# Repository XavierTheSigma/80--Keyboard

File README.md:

# Keyboard
My Keyboard is a standard 80% keyboard with an added Rotary Encoder for volume control.

I made this Keyboard for myself, And to learn. This was my first time using Chip on Board tech, so it was quite a challenge for me, but it helped me learn alot.

## Features:
- 80% Keyboard
- 87 Keys
- Rotary Encoder 
- Arrow Keys
- F Keys
- Chip On Board

## CAD Model:
I designed the Case to fit together with 3 pieces and 8 M2.5 screws. The 3 pieces are the Bottom of the case, The sides of the case (with a cutout for the USB-C) and the Top of the case, which includes the switch plate and the Top Frame. The Bottom and Sides are clearance holes and the screw threads into the top. The screw threads into 1.4mm of the top part and the screws are actually held .5mm higher than the bottom instead of flush.

## PCB:
I made my PCB in KiCad. This was my first time using CoB, Chip on Board, where instead of using a microcontroller, The RP2040 chip is directly on the board with all the other necessary components. I ended up reffereing to [RP2040 Datasheet](https://pip.raspberrypi.com/documents/RP-008371-DS-rp2040-datasheet.pdf) alot for this. 

Here is the Schematic, I spend alot of time figuring out how to get the whole CoB system working, but I think I did well.

Here is the PCB, I think I was able to make it pretty Compact with the components, however I am still unsure about the USB-C port.

## Firmware:
I decided on [KMK](https://github.com/KMKfw/kmk_firmware) firmware for this keyboard, as it is quite easy to code and implement.

## BOM:
|Name                    |Purpose                     |Quantity|Total Cost (USD)|Link                                                                                                                                                                                                                                                                                                                                                                                                                                                                                                                                                                                                                                                                           |Distributor|
|------------------------|----------------------------|--------|----------------|-------------------------------------------------------------------------------------------------------------------------------------------------------------------------------------------------------------------------------------------------------------------------------------------------------------------------------------------------------------------------------------------------------------------------------------------------------------------------------------------------------------------------------------------------------------------------------------------------------------------------------------------------------------------------------|-----------|
|M2.5x12mm Screws        |Hold the Case Together      |100     |4.29            |https://www.aliexpress.com/item/1005006149650871.html?spm=a2g0o.productlist.main.7.351a5435pfKSzT&algo_pvid=73726b03-3458-4531-a617-164769dc475a&algo_exp_id=73726b03-3458-4531-a617-164769dc475a-6&pdp_ext_f=%7B%22order%22%3A%22815%22%2C%22spu_best_type%22%3A%22price%22%2C%22eval%22%3A%221%22%2C%22fromPage%22%3A%22search%22%7D&pdp_npi=6%40dis%21AUD%214.29%214.29%21%21%2120.05%2120.05%21%4021033d9d17748774623062062ebf6b%2112000035985037198%21sea%21AU%216079532204%21X%211%210%21n_tag%3A-29919%3Bd%3A8c80d33f%3Bm03_new_user%3A-29895&curPageLogUid=wg6dSTH9tu8G&utparam-url=scene%3Asearch%7Cquery_from%3A%7Cx_object_id%3A1005006149650871%7C_p_origin_prod%3A|Aliexpress |
|PCBA                    |Printed Circuit Board       |2       |53.90           |https://cart.jlcpcb.com/shopcart/cart                                                                                                                                                                                                                                                                                                                                                                                                                                                                                                                                                                                                                                          |JLCPCB     |
|3x4mm SMD tactile switch|BOOT and RESET              |100     |3.04            |https://www.aliexpress.com/item/1005005551946922.html?spm=a2g0o.cart.0.0.6cea38daTwsp4M&mp=1&pdp_npi=6%40dis%21AUD%21AUD%204.43%21AUD%204.43%21%21AUD%204.34%21%21%21%402103274e17748741857928605e241d%2112000033511703865%21ct%21AU%216079532204%21%211%210%21                                                                                                                                                                                                                                                                                                                                                                                                                |Aliexpress |
|Hotswap Sockets         |For the switches to go into.|110     |6.78            |https://www.aliexpress.com/item/1005007232040760.html?spm=a2g0o.cart.0.0.691238daXmoF8z&mp=1&pdp_npi=6%40dis%21AUD%21AUD%2021.04%21AUD%209.89%21%21AUD%209.79%21%21%21%402101d6ff17748726457652554ef3f5%2112000039893759777%21ct%21AU%216079532204%21%211%210%21                                                                                                                                                                                                                                                                                                                                                                                                               |Aliexpress |
|Rotary Encoder          |Volume Control              |2       |2.33            |https://www.aliexpress.com/item/1005009360298765.html?spm=a2g0o.cart.0.0.691238daXmoF8z&mp=1&pdp_npi=6%40dis%21AUD%21AUD%207.09%21AUD%203.40%21%21AUD%203.37%21%21%21%402101d6ff17748726457652554ef3f5%2112000049239221996%21ct%21AU%216079532204%21%211%210%21                                                                                                                                                                                                                                                                                                                                                                                                                |Aliexpress |
|Mechanical Switches     |Register Keystrokes         |90      |11.10           |https://www.aliexpress.com/item/1005010733013518.html?spm=a2g0o.cart.0.0.691238daXmoF8z&mp=1&pdp_npi=6%40dis%21AUD%21AUD%205.39%21AUD%205.39%21%21AUD%205.39%21%21%21%402101d6ff17748726457652554ef3f5%2112000053347971169%21ct%21AU%216079532204%21%213%210%21                                                                                                                                                                                                                                                                                                                                                                                                                |Aliexpress |
|Keycap Set              |To press on                 |1       |12.61           |https://www.aliexpress.com/item/1005009316481772.html?spm=a2g0o.cart.0.0.691238daXmoF8z&mp=1&pdp_npi=6%40dis%21AUD%21AUD%2018.39%21AUD%2018.39%21%21AUD%2018.39%21%21%21%402101d6ff17748723426904626ef3f5%2112000048726412320%21ct%21AU%216079532204%21%211%210%21                                                                                                                                                                                                                                                                                                                                                                                                             |Aliexpress |
|Stabilizers             |Prevent Wobbling            |1       |2.60            |https://www.aliexpress.com/item/1005007212869086.html?spm=a2g0o.cart.0.0.691238daXmoF8z&mp=1&pdp_npi=6%40dis%21AUD%21AUD%203.79%21AUD%203.79%21%21AUD%203.79%21%21%21%402101d6ff17748723426904626ef3f5%2112000039826435204%21ct%21AU%216079532204%21%211%210%21                                                                                                                                                                                                                                                                                                                                                                                                                |Aliexpress |
|1N5819 Diode (SMD)      |Diodes for Matrix           |100     |2.03            |https://www.aliexpress.com/item/1005010391501956.html?mp=1&pdp_npi=6%40dis%21AUD%21AUD%202.96%21AUD%202.96%21%21AUD%202.87%21%21%21%402101d6ff17748723426904626ef3f5%2112000052256220506%21ct%21AU%216079532204%21%211%210%21                                                                                                                                                                                                                                                                                                                                                                                                                                                  |Aliexpress |
|                        |                            |        |                |                                                                                                                                                                                                                                                                                                                                                                                                                                                                                                                                                                                                                                                                               |           |

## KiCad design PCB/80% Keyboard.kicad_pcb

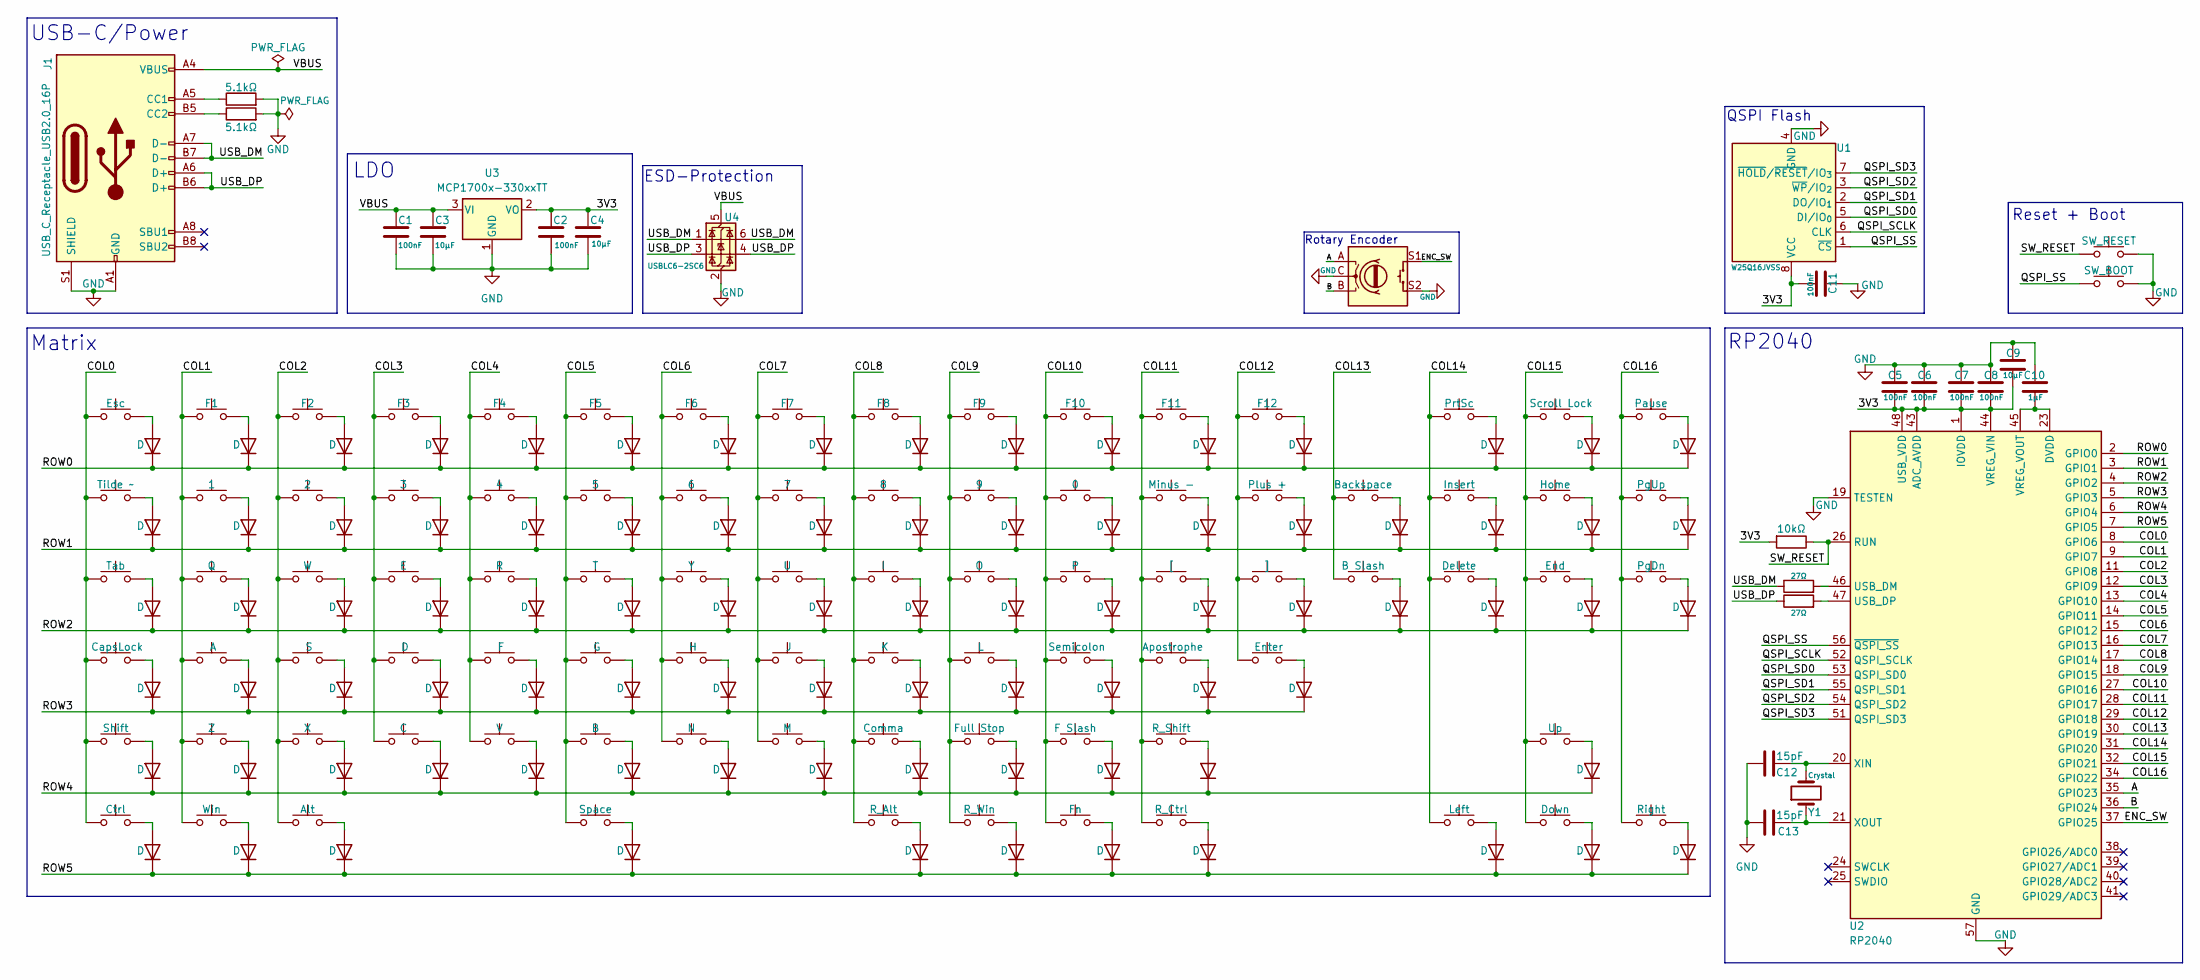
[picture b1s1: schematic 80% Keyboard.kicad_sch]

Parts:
C1, C2, C5, C6, C7, C8, C11: 100nF; C_0402_1005Metric_Pad0.74x0.62mm_HandSolder
C3, C4, C9: 10µF; C_0402_1005Metric_Pad0.74x0.62mm_HandSolder
C10: 1µF; C_0402_1005Metric_Pad0.74x0.62mm_HandSolder
C12, C13: 15pF; C_0402_1005Metric_Pad0.74x0.62mm_HandSolder
D1, D2, D3, D4, D5, D6, D7, D8, D9, D10, D11, D12, D13, D14, D15, D16, D17, D18, D19, D20, D21, D22, D23, D25, D26, D27, D28, D29, D31, D32, D33, D34, D35, D36, D37, D38, D39, D40, D41, D43, D44, D45, D46, D47, D49, D50, D51, D52, D53, D54, D55, D56, D57, D58, D59, D60, D61, D62, D63, D64, D65, D66, D67, D68, D69, D70, D71, D72, D73, D74, D75, D76, D80, D81, D85, D86, D87, D90, D91, D92, D93, D95, D96, D97, D98, D99, D102: D; D_SOD-123
J1: USB_C_Receptacle_USB2.0_16P; USB_C_Receptacle_GCT_USB4105-xx-A_16P_TopMnt_Horizontal
R1, R2: 5.1kΩ; R_0402_1005Metric_Pad0.72x0.64mm_HandSolder
R3: 10kΩ; R_0402_1005Metric_Pad0.72x0.64mm_HandSolder
R4, R5: 27Ω; R_0402_1005Metric_Pad0.72x0.64mm_HandSolder
SW1: Esc; MX-Hotswap-1U
SW2: Tilde ~; MX-Hotswap-1U
SW3: Tab; MX-Hotswap-1.5U
SW4: CapsLock; MX-Hotswap-1.75U
SW5: Shift; MX-Hotswap-2.25U
SW6: Ctrl; MX-Hotswap-1.25U
SW7: F1; MX-Hotswap-1U
SW8: 1; MX-Hotswap-1U
SW9: Q; MX-Hotswap-1U
SW10: A; MX-Hotswap-1U
SW11: Z; MX-Hotswap-1U
SW12: Win; MX-Hotswap-1.25U
SW13: F2; MX-Hotswap-1U
SW14: 2; MX-Hotswap-1U
SW15: W; MX-Hotswap-1U
SW16: S; MX-Hotswap-1U
SW17: X; MX-Hotswap-1U
SW18: Alt; MX-Hotswap-1.25U
SW19: F3; MX-Hotswap-1U
SW20: 3; MX-Hotswap-1U
SW21: E; MX-Hotswap-1U
SW22: D; MX-Hotswap-1U
SW23: C; MX-Hotswap-1U
SW24: RotaryEncoder; RotaryEncoder_Alps_EC11E-Switch_Vertical_H20mm
SW25: F4; MX-Hotswap-1U
SW26: 4; MX-Hotswap-1U
SW27: R; MX-Hotswap-1U
SW28: F; MX-Hotswap-1U
SW29: V; MX-Hotswap-1U
SW30: SW_BOOT; SW_Push_1P1T_NO_Vertical_Wuerth_434133025816
SW31: F5; MX-Hotswap-1U
SW32: 5; MX-Hotswap-1U
SW33: T; MX-Hotswap-1U
SW34: G; MX-Hotswap-1U
SW35: B; MX-Hotswap-1U
SW36: Space; MX-Hotswap-6.25U
SW37: F6; MX-Hotswap-1U
SW38: 6; MX-Hotswap-1U
SW39: Y; MX-Hotswap-1U
SW40: H; MX-Hotswap-1U
SW41: N; MX-Hotswap-1U
SW42: SW_RESET; SW_Push_1P1T_NO_Vertical_Wuerth_434133025816
SW43: F7; MX-Hotswap-1U
SW44: 7; MX-Hotswap-1U
SW45: U; MX-Hotswap-1U
SW46: J; MX-Hotswap-1U
SW47: M; MX-Hotswap-1U
SW49: F8; MX-Hotswap-1U
SW50: 8; MX-Hotswap-1U
SW51: I; MX-Hotswap-1U
SW52: K; MX-Hotswap-1U
SW53: Comma; MX-Hotswap-1U
SW54: R_Alt; MX-Hotswap-1.25U
SW55: F9; MX-Hotswap-1U
SW56: 9; MX-Hotswap-1U
SW57: O; MX-Hotswap-1U
SW58: L; MX-Hotswap-1U
SW59: Full Stop; MX-Hotswap-1U
SW60: R_Win; MX-Hotswap-1.25U
SW61: F10; MX-Hotswap-1U
SW62: 0; MX-Hotswap-1U
SW63: P; MX-Hotswap-1U
SW64: Semicolon; MX-Hotswap-1U
SW65: F Slash; MX-Hotswap-1U
SW66: Fn; MX-Hotswap-1.25U
SW67: F11; MX-Hotswap-1U
SW68: Minus -; MX-Hotswap-1U
SW69: [; MX-Hotswap-1U
SW70: Apostrophe; MX-Hotswap-1U
SW71: R_Shift; MX-Hotswap-2.75U
SW72: R_Ctrl; MX-Hotswap-1.25U
SW73: F12; MX-Hotswap-1U
SW74: Plus +; MX-Hotswap-1U
SW75: ]; MX-Hotswap-1U
SW76: Enter; MX-Hotswap-2.25U
SW80: Backspace; MX-Hotswap-2U
SW81: B Slash; MX-Hotswap-1.5U
SW85: PrtSc; MX-Hotswap-1U
SW86: Insert; MX-Hotswap-1U
SW87: Delete; MX-Hotswap-1U
SW90: Left; MX-Hotswap-1U
SW91: Scroll Lock; MX-Hotswap-1U
SW92: Home; MX-Hotswap-1U
SW93: End; MX-Hotswap-1U
SW95: Up; MX-Hotswap-1U
SW96: Down; MX-Hotswap-1U
SW97: Pause; MX-Hotswap-1U
SW98: PgUp; MX-Hotswap-1U
SW99: PgDn; MX-Hotswap-1U
SW102: Right; MX-Hotswap-1U
U1: W25Q16JVSS; SOIC-8_3.9x4.9mm_P1.27mm
U2: RP2040; QFN-56-1EP_7x7mm_P0.4mm_EP3.2x3.2mm
U3: MCP1700x-330xxTT; SOT-23
U4: USBLC6-2SC6; SOT-23-6
Y1: Crystal; Crystal_SMD_3225-4Pin_3.2x2.5mm_HandSoldering

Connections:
/3V3: C2.1, C4.1, C5.2, C6.2, C7.2, C8.2, C9.2, C11.2, R3.2, U1.8 (VCC), U2.1 (IOVDD), U2.10 (IOVDD), U2.22 (IOVDD), U2.33 (IOVDD), U2.42 (IOVDD), U2.43 (ADC_AVDD), U2.44 (VREG_VIN), U2.48 (USB_VDD), U2.49 (IOVDD), U3.2 (VO)
/A: SW24.A, U2.35 (GPIO23)
/B: SW24.B, U2.36 (GPIO24)
/COL0: SW1.1, SW2.1, SW3.1, SW4.1, SW5.1, SW6.1, U2.8 (GPIO6)
/COL1: SW7.1, SW8.1, SW9.1, SW10.1, SW11.1, SW12.1, U2.9 (GPIO7)
/COL2: SW13.1, SW14.1, SW15.1, SW16.1, SW17.1, SW18.1, U2.11 (GPIO8)
/COL3: SW19.1, SW20.1, SW21.1, SW22.1, SW23.1, U2.12 (GPIO9)
/COL4: SW25.1, SW26.1, SW27.1, SW28.1, SW29.1, U2.13 (GPIO10)
/COL5: SW31.1, SW32.1, SW33.1, SW34.1, SW35.1, SW36.1, U2.14 (GPIO11)
/COL6: SW37.1, SW38.1, SW39.1, SW40.1, SW41.1, U2.15 (GPIO12)
/COL7: SW43.1, SW44.1, SW45.1, SW46.1, SW47.1, U2.16 (GPIO13)
/COL8: SW49.1, SW50.1, SW51.1, SW52.1, SW53.1, SW54.1, U2.17 (GPIO14)
/COL9: SW55.1, SW56.1, SW57.1, SW58.1, SW59.1, SW60.1, U2.18 (GPIO15)
/COL10: SW61.1, SW62.1, SW63.1, SW64.1, SW65.1, SW66.1, U2.27 (GPIO16)
/COL11: SW67.1, SW68.1, SW69.1, SW70.1, SW71.1, SW72.1, U2.28 (GPIO17)
/COL12: SW73.1, SW74.1, SW75.1, SW76.1, U2.29 (GPIO18)
/COL13: SW80.1, SW81.1, U2.30 (GPIO19)
/COL14: SW85.1, SW86.1, SW87.1, SW90.1, U2.31 (GPIO20)
/COL15: SW91.1, SW92.1, SW93.1, SW95.1, SW96.1, U2.32 (GPIO21)
/COL16: SW97.1, SW98.1, SW99.1, SW102.1, U2.34 (GPIO22)
/ENC_SW: SW24.S1, U2.37 (GPIO25)
/QSPI_SCLK: U1.6 (CLK), U2.52 (QSPI_SCLK)
/QSPI_SD0: U1.5 (DI/IO_{0}), U2.53 (QSPI_SD0)
/QSPI_SD1: U1.2 (DO/IO_{1}), U2.55 (QSPI_SD1)
/QSPI_SD2: U1.3 (~WP/IO_{2}), U2.54 (QSPI_SD2)
/QSPI_SD3: U1.7 (~HOLD/~RESET/IO_{3}), U2.51 (QSPI_SD3)
/QSPI_SS: SW30.1, U1.1 (~CS), U2.56 (~QSPI_SS)
/ROW0: D1.1 (K), D7.1 (K), D13.1 (K), D19.1 (K), D25.1 (K), D31.1 (K), D37.1 (K), D43.1 (K), D49.1 (K), D55.1 (K), D61.1 (K), D67.1 (K), D73.1 (K), D85.1 (K), D91.1 (K), D97.1 (K), U2.2 (GPIO0)
/ROW1: D2.1 (K), D8.1 (K), D14.1 (K), D20.1 (K), D26.1 (K), D32.1 (K), D38.1 (K), D44.1 (K), D50.1 (K), D56.1 (K), D62.1 (K), D68.1 (K), D74.1 (K), D80.1 (K), D86.1 (K), D92.1 (K), D98.1 (K), U2.3 (GPIO1)
/ROW2: D3.1 (K), D9.1 (K), D15.1 (K), D21.1 (K), D27.1 (K), D33.1 (K), D39.1 (K), D45.1 (K), D51.1 (K), D57.1 (K), D63.1 (K), D69.1 (K), D75.1 (K), D81.1 (K), D87.1 (K), D93.1 (K), D99.1 (K), U2.4 (GPIO2)
/ROW3: D4.1 (K), D10.1 (K), D16.1 (K), D22.1 (K), D28.1 (K), D34.1 (K), D40.1 (K), D46.1 (K), D52.1 (K), D58.1 (K), D64.1 (K), D70.1 (K), D76.1 (K), U2.5 (GPIO3)
/ROW4: D5.1 (K), D11.1 (K), D17.1 (K), D23.1 (K), D29.1 (K), D35.1 (K), D41.1 (K), D47.1 (K), D53.1 (K), D59.1 (K), D65.1 (K), D71.1 (K), D95.1 (K), U2.6 (GPIO4)
/ROW5: D6.1 (K), D12.1 (K), D18.1 (K), D36.1 (K), D54.1 (K), D60.1 (K), D66.1 (K), D72.1 (K), D90.1 (K), D96.1 (K), D102.1 (K), U2.7 (GPIO5)
/SW_RESET: R3.1, SW42.1, U2.26 (RUN)
/USB_DM: J1.A7 (D-), J1.B7 (D-), R4.1, U4.1 (I/O1), U4.6 (I/O1)
/USB_DP: J1.A6 (D+), J1.B6 (D+), R5.1, U4.3 (I/O2), U4.4 (I/O2)
/VBUS: C1.1, C3.1, J1.A4 (VBUS), J1.A9 (VBUS), J1.B4 (VBUS), J1.B9 (VBUS), U3.3 (VI), U4.5 (VBUS)
GND: C1.2, C2.2, C3.2, C4.2, C5.1, C6.1, C7.1, C8.1, C9.1, C10.1, C11.1, C12.1, C13.1, J1.A1 (GND), J1.A12 (GND), J1.B1 (GND), J1.B12 (GND), J1.S1 (SHIELD), R1.2, R2.2, SW24.C, SW24.S2, SW30.2, SW42.2, U1.4 (GND), U2.19 (TESTEN), U2.57 (GND), U3.1 (GND), U4.2 (GND), Y1.3, Y1.4
unnamed: D1.2 (A), SW1.2
unnamed: D2.2 (A), SW2.2
unnamed: D3.2 (A), SW3.2
unnamed: D4.2 (A), SW4.2
unnamed: D5.2 (A), SW5.2
unnamed: D6.2 (A), SW6.2
unnamed: D7.2 (A), SW7.2
unnamed: D8.2 (A), SW8.2
unnamed: D9.2 (A), SW9.2
unnamed: D10.2 (A), SW10.2
unnamed: D11.2 (A), SW11.2
unnamed: D12.2 (A), SW12.2
unnamed: D13.2 (A), SW13.2
unnamed: D14.2 (A), SW14.2
unnamed: D15.2 (A), SW15.2
unnamed: D16.2 (A), SW16.2
unnamed: D17.2 (A), SW17.2
unnamed: D18.2 (A), SW18.2
unnamed: D19.2 (A), SW19.2
unnamed: D20.2 (A), SW20.2
unnamed: D21.2 (A), SW21.2
unnamed: D22.2 (A), SW22.2
unnamed: D23.2 (A), SW23.2
unnamed: D25.2 (A), SW25.2
unnamed: D26.2 (A), SW26.2
unnamed: D27.2 (A), SW27.2
unnamed: D28.2 (A), SW28.2
unnamed: D29.2 (A), SW29.2
unnamed: D31.2 (A), SW31.2
unnamed: D32.2 (A), SW32.2
unnamed: D33.2 (A), SW33.2
unnamed: D34.2 (A), SW34.2
unnamed: D35.2 (A), SW35.2
unnamed: D36.2 (A), SW36.2
unnamed: D37.2 (A), SW37.2
unnamed: D38.2 (A), SW38.2
unnamed: D39.2 (A), SW39.2
unnamed: D40.2 (A), SW40.2
unnamed: D41.2 (A), SW41.2
unnamed: D43.2 (A), SW43.2
unnamed: D44.2 (A), SW44.2
unnamed: D45.2 (A), SW45.2
unnamed: D46.2 (A), SW46.2
unnamed: D47.2 (A), SW47.2
unnamed: D49.2 (A), SW49.2
unnamed: D50.2 (A), SW50.2
unnamed: D51.2 (A), SW51.2
unnamed: D52.2 (A), SW52.2
unnamed: D53.2 (A), SW53.2
unnamed: D54.2 (A), SW54.2
unnamed: D55.2 (A), SW55.2
unnamed: D56.2 (A), SW56.2
unnamed: D57.2 (A), SW57.2
unnamed: D58.2 (A), SW58.2
unnamed: D59.2 (A), SW59.2
unnamed: D60.2 (A), SW60.2
unnamed: D61.2 (A), SW61.2
unnamed: D62.2 (A), SW62.2
unnamed: D63.2 (A), SW63.2
unnamed: D64.2 (A), SW64.2
unnamed: D65.2 (A), SW65.2
unnamed: D66.2 (A), SW66.2
unnamed: D67.2 (A), SW67.2
unnamed: D68.2 (A), SW68.2
unnamed: D69.2 (A), SW69.2
unnamed: D70.2 (A), SW70.2
unnamed: D71.2 (A), SW71.2
unnamed: D72.2 (A), SW72.2
unnamed: D73.2 (A), SW73.2
unnamed: D74.2 (A), SW74.2
unnamed: D75.2 (A), SW75.2
unnamed: D76.2 (A), SW76.2
unnamed: D80.2 (A), SW80.2
unnamed: D81.2 (A), SW81.2
unnamed: D85.2 (A), SW85.2
unnamed: D86.2 (A), SW86.2
unnamed: D87.2 (A), SW87.2
unnamed: D90.2 (A), SW90.2
unnamed: D91.2 (A), SW91.2
unnamed: D92.2 (A), SW92.2
unnamed: D93.2 (A), SW93.2
unnamed: D95.2 (A), SW95.2
unnamed: D96.2 (A), SW96.2
unnamed: D97.2 (A), SW97.2
unnamed: D98.2 (A), SW98.2
unnamed: D99.2 (A), SW99.2
unnamed: D102.2 (A), SW102.2
unnamed: J1.A5 (CC1), R1.1
unnamed: J1.B5 (CC2), R2.1
unnamed: R4.2, U2.46 (USB_DM)
unnamed: R5.2, U2.47 (USB_DP)
unnamed: C10.2, U2.23 (DVDD), U2.45 (VREG_VOUT), U2.50 (DVDD)
unnamed: C12.2, U2.20 (XIN), Y1.2
unnamed: C13.2, U2.21 (XOUT), Y1.1

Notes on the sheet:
Reset + Boot
Rotary Encoder
RP2040
ESD-Protection
Matrix
USB-C/Power
QSPI Flash
LDO

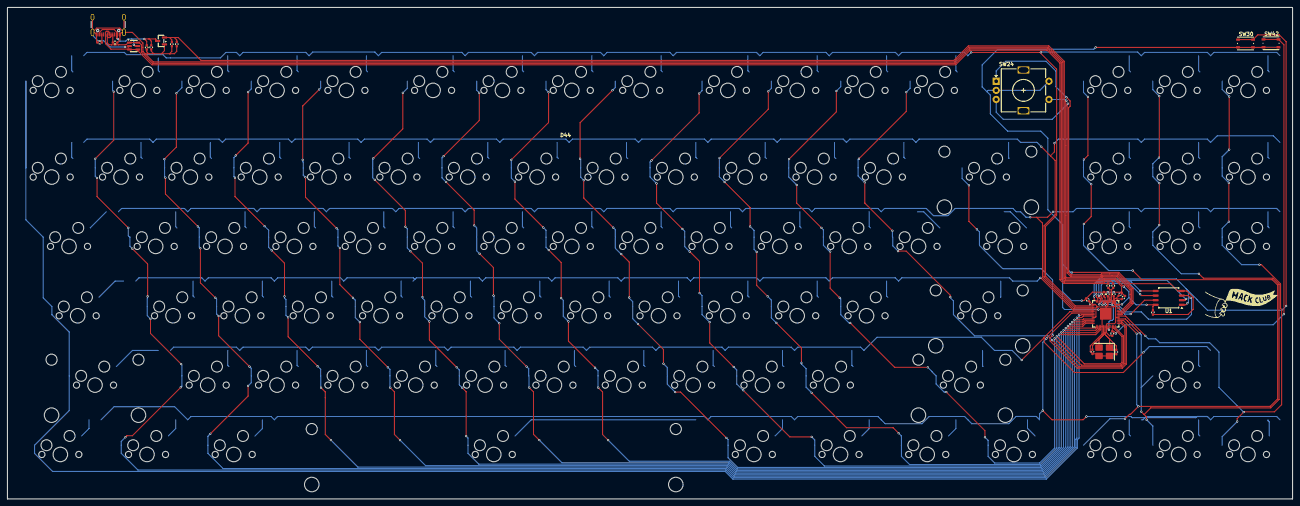
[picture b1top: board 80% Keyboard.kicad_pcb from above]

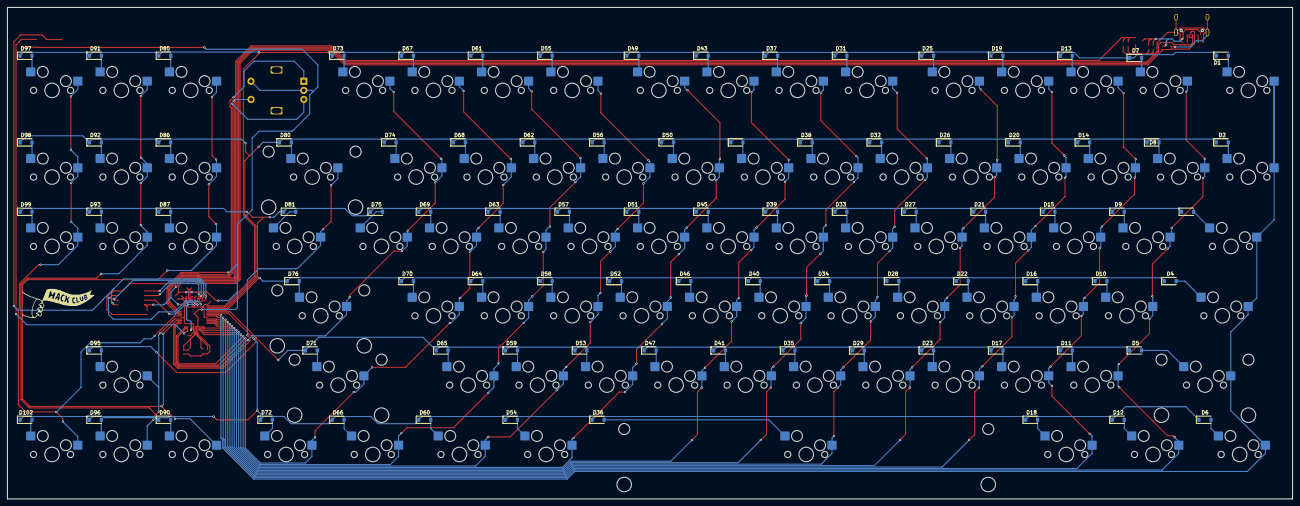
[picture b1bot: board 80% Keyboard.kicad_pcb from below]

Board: 2 copper layers, 353.0 x 135.0 mm, 201 parts (174 on the bottom side), 132 nets.

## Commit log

2026-03-19 Structure + PCB
2026-03-19 New Journal Entry
2026-03-19 Added Crystal
2026-03-23 Entire PCB + Updated Journal.MD
2026-03-23 Artwork + Name + Journal
2026-03-30 All of CAD Case + Clean Up of PCB Files
2026-03-30 Information Proto
2026-03-30 Journal Fix
2026-03-30 Added PCB img
2026-03-30 Bom Stuff
2026-03-31 All of BOM pretty much
2026-03-31 Small Journal Update
2026-03-31 Keyboard Bottom Adjustments
2026-03-31 Firmware
2026-03-31 Firmware update
